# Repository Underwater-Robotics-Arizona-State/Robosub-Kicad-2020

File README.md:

# Robosub-Kicad-2020
Electrical Team Kicad file

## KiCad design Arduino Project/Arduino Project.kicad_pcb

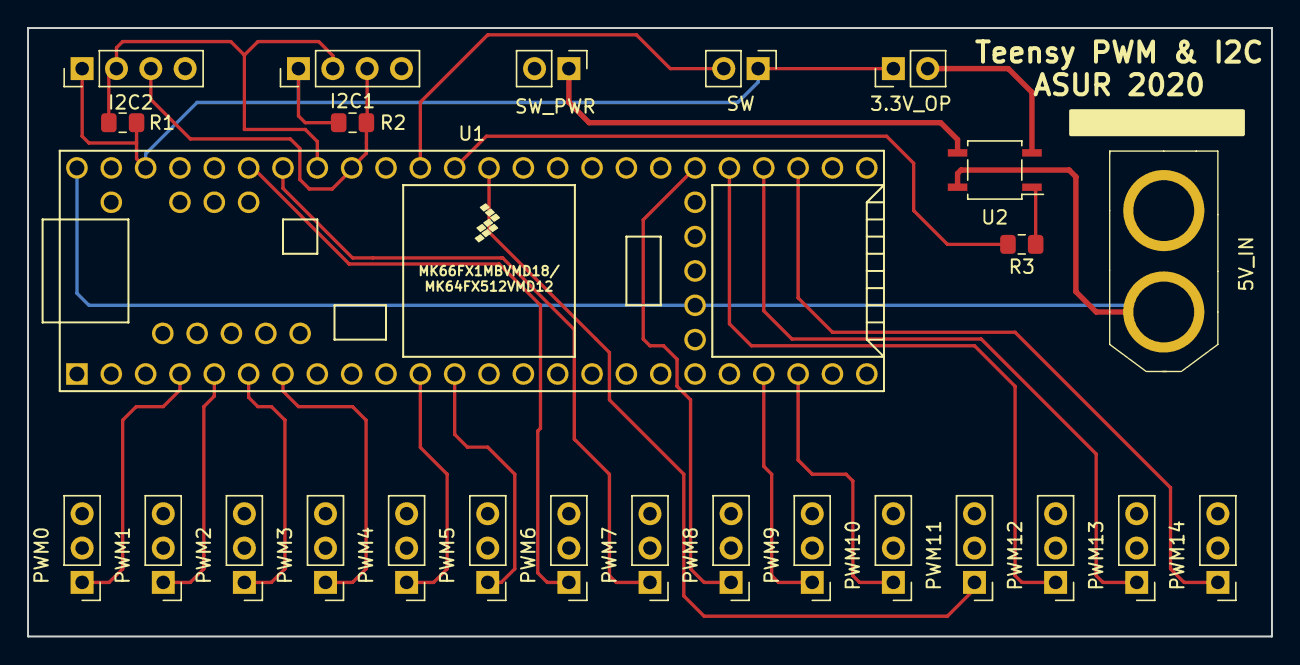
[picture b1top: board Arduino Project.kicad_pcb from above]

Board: 2 copper layers, 92.0 x 45.0 mm, 26 parts (0 on the bottom side), 24 nets.

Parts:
3.3V_OP: Conn_01x02; PinHeader_1x02_P2.54mm_Vertical
5V_IN: Conn_01x02; XT60
I2C1, I2C2: Conn_01x04; PinHeader_1x04_P2.54mm_Vertical
PWM0, PWM1, PWM2, PWM3, PWM4, PWM5, PWM6, PWM7, PWM8, PWM9, PWM10, PWM11, PWM12, PWM13, PWM14: Conn_01x03; PinHeader_1x03_P2.54mm_Vertical
R1, R2, R3: R; R_0805_2012Metric_Pad1.15x1.40mm_HandSolder
SW: Conn_01x02; PinHeader_1x02_P2.54mm_Vertical
SW_PWR: Conn_01x02; PinHeader_1x02_P2.54mm_Vertical
U1: Teensy3.5; Teensy35_36
U2: NSL-32; SOP-4_3.8x4.1mm_P2.54mm

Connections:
+3V3: 3.3V_OP.1, I2C1.1, I2C2.1, R1.1, R2.1, SW.1, U1.51
+5V: 5V_IN.1, U1.26, U1.53, U2.4
CBEnable: R3.2, U1.42
CBEnable_5v: SW_PWR.1, U2.3
GND: 3.3V_OP.2, 5V_IN.2, I2C1.4, I2C2.4, PWM0.3, PWM1.3, PWM2.3, PWM3.3, PWM4.3, PWM5.3, PWM6.3, PWM7.3, PWM8.3, PWM9.3, PWM10.3, PWM11.3, PWM12.3, PWM13.3, PWM14.3, SW_PWR.2, U1.27, U2.2
I2C_SCL: I2C1.2, I2C2.2, R1.2, U1.46
I2C_SDA: I2C1.3, I2C2.3, R2.2, U1.45
unnamed: R3.1, U2.1
PWM_0: PWM0.1, U1.4
PWM_1: PWM1.1, U1.5
PWM_2: PWM2.1, U1.6
PWM_3: PWM3.1, U1.7
PWM_4: PWM4.1, U1.11
PWM_5: PWM5.1, U1.12
PWM_6: PWM6.1, U1.48
PWM_7: PWM7.1, U1.47
PWM_8: PWM8.1, U1.35
PWM_9: PWM9.1, U1.21
PWM_10: PWM10.1, U1.22
PWM_11: PWM11.1, U1.41
PWM_12: PWM12.1, U1.34
PWM_13: PWM13.1, U1.33
PWM_14: PWM14.1, U1.32
Saftey_Switch: SW.2, U1.43

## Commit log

2019-10-04 First Repo push
2019-10-06 Final sch ready for review
2019-10-07 Board Prototrype
    e
2019-10-10 eeeeeeeeeeeee
    eeeeeeeeeeeeeee
2019-10-12 Final Board
2019-10-12 Final v2
    e
2019-10-13 Made power board project
2019-10-13 Sch Update
2019-10-23 final
